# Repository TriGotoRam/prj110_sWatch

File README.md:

My custom sWatch in standart china case. main CPU - ESP32. LCD - 160*80 16bit color + accelerometer + IRRED pulse meter.
Contains:
Eagle pcb
ESP32 sorces

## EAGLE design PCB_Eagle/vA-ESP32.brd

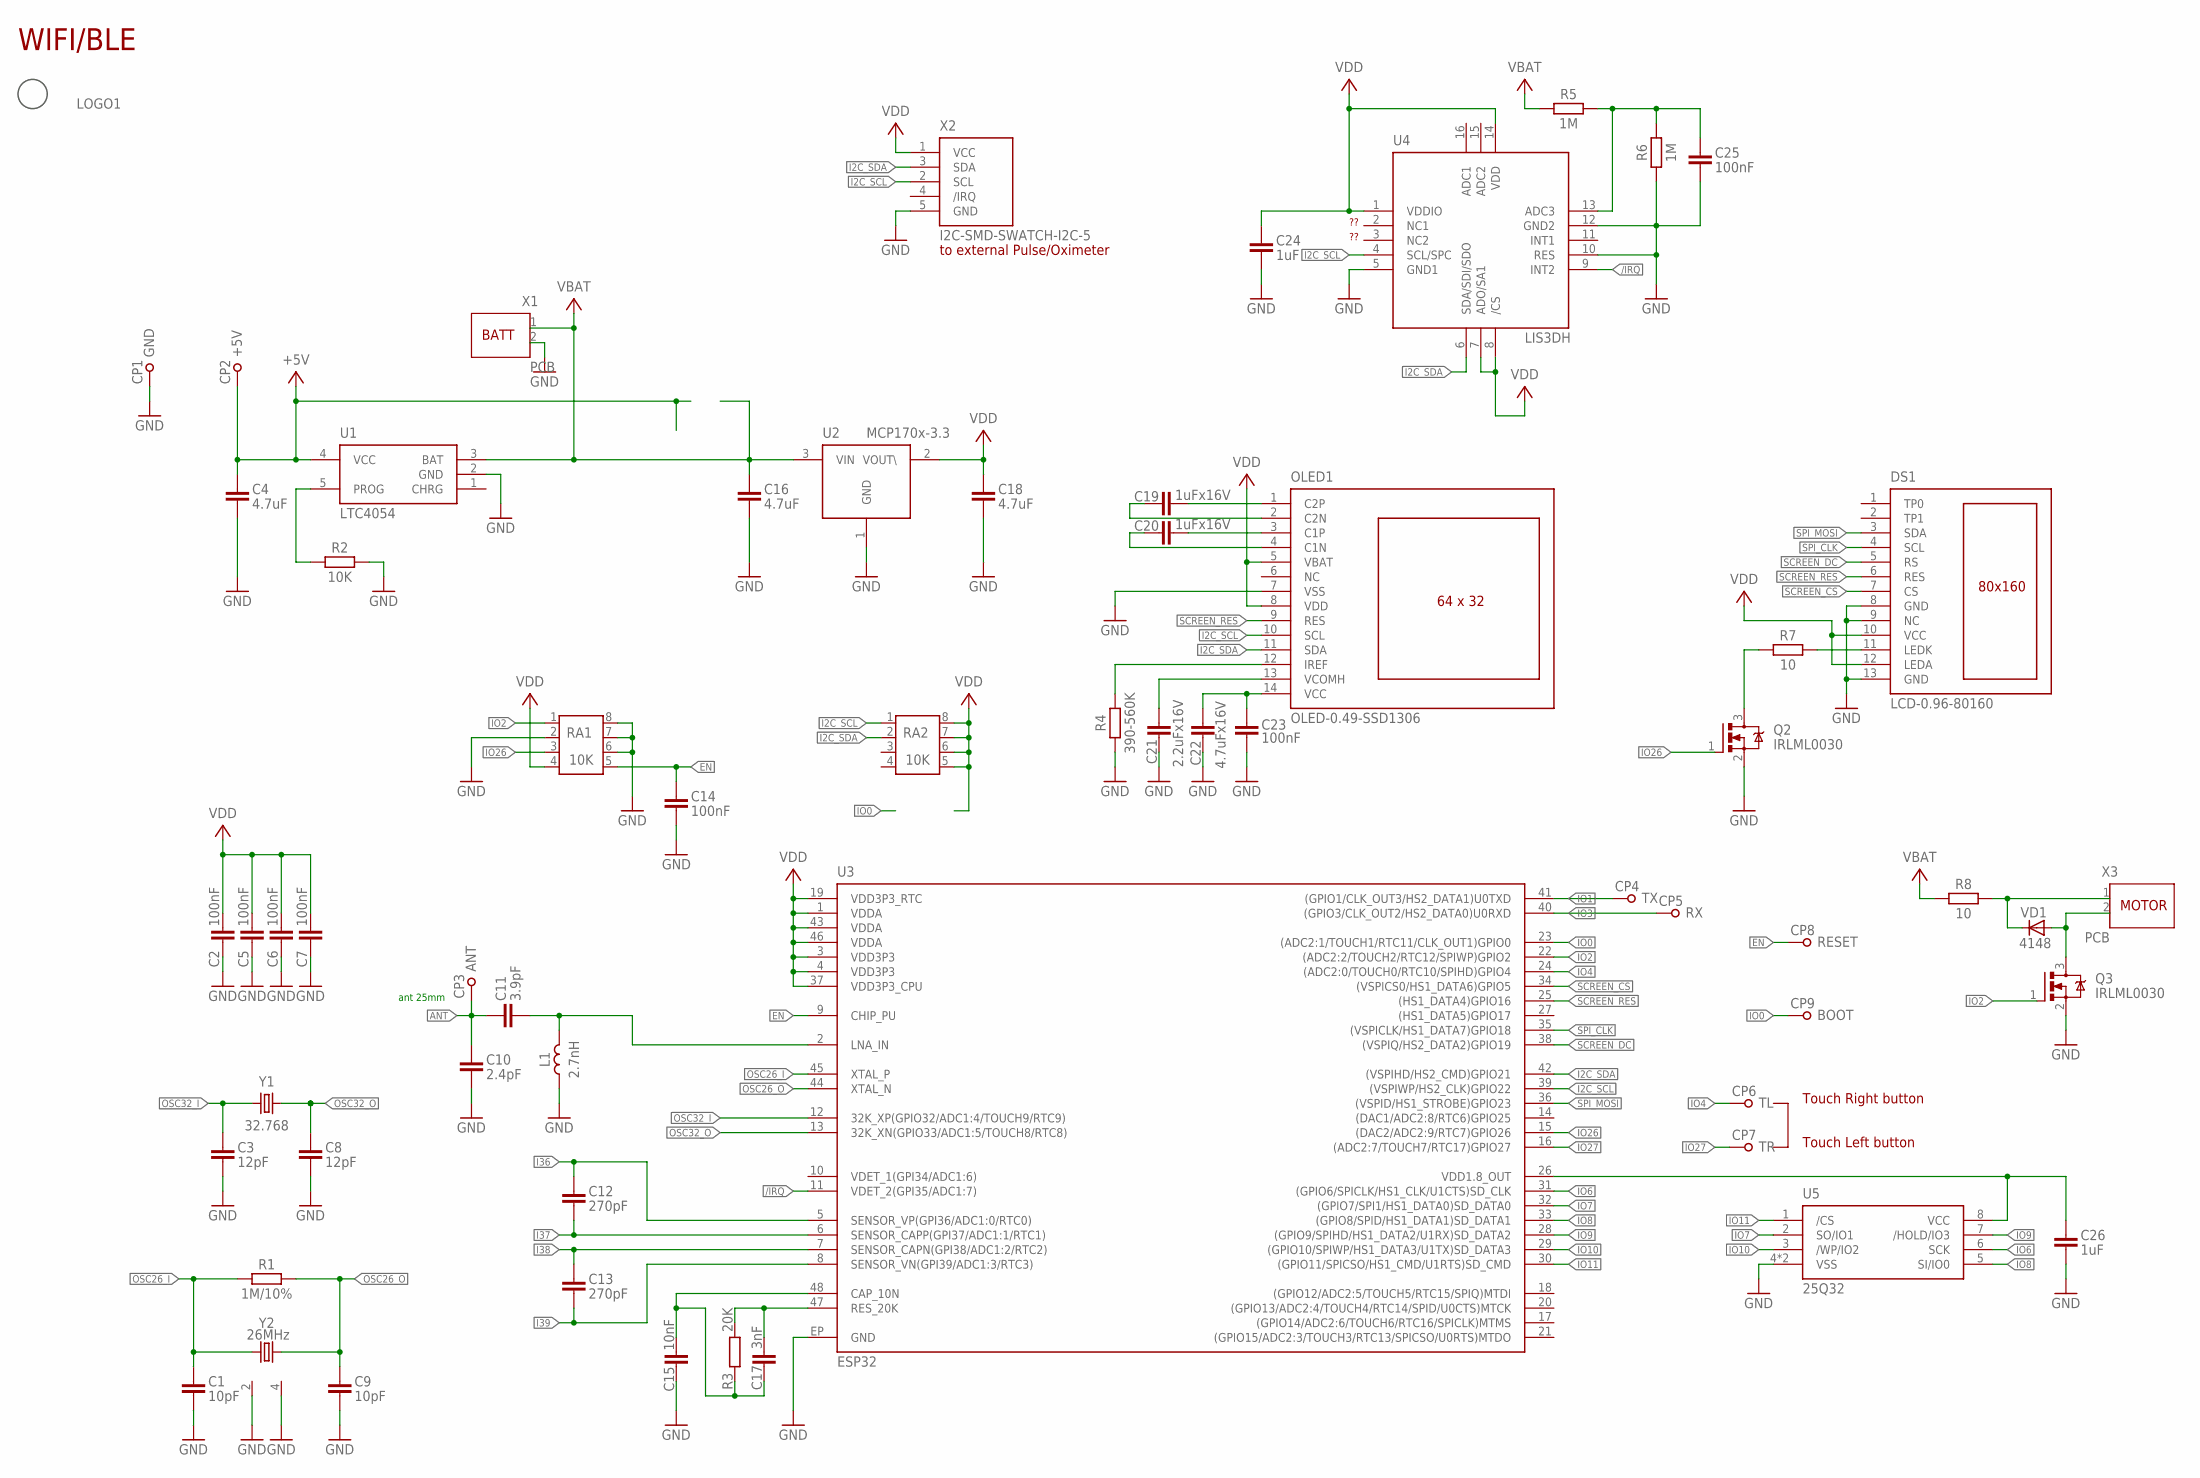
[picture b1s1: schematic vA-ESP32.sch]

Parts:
C1, C9: 10pF; C0402
C2, C6, C7, C14, C25: 100nF; C0402
C3, C8: 12pF; C0402
C4, C16, C18: 4.7uF; C0603
C5, C23: 100nF; C0603
C10: 2.4pF; C0402
C11: 3.9pF; C0402
C12, C13: 270pF; C0402
C15: 10nF; C0402
C17: 3nF; C0402
C19, C20: 1uFx16V; C0603
C21: 2.2uFx16V; C0805
C22: 4.7uFx16V; C0805
C24: 1uF; C0402
C26: 1uF; C0603
CP1: GND; CP-1-R08MM
CP2: +5V; CP-1-R08MM
CP3: ANT; CP-1-C08MM
CP4: TX; CP-1-C08MM
CP5: RX; CP-1-C08MM
CP6: TL; CP-1-C24MM
CP7: TR; CP-1-C24MM
CP8: RESET; CP-1-C08MM
CP9: BOOT; CP-1-C08MM
DS1: LCD-0.96-80160; LCD-0.96-80*160
FIDUCIAL1: FIDUCIAL-MICRO
L1: 2.7nH; L0402
LOGO1: LOGO6; LOGO_OMEGA
OLED1: OLED-0.49-SSD1306; OLED_0.49-SSD1306
Q2, Q3: IRLML0030; SOT23-3-1
R1: 1M/10%; R0402
R2: 10K; R0402
R3: 20K; R0402
R4: 390-560K; R0603
R5, R6: 1M; R0402
R7, R8: 10; R0603
RA1, RA2: 10K; EXB28V
U1: LTC4054; SOT23-5L
U2: MCP170x-3.3; SOT23-3
U3: ESP32; QFN48-6X6-0.4MM
U4: LIS3DH; LGA16
U5: 25Q32; USON-8-2X3
VD1: 4148; SOD523
X1, X3: PCB; 2C_SMD-SWATCH
X2: I2C-SMD-SWATCH-I2C-5; SMD-SWATCH-I2C-5
Y1: 32.768; XTAL3215
Y2: 26MHz; CRYSTAL-SMD-3225

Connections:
+5V: C4.1, CP2.1, U1.4 (VCC)
/IRQ: U3.11 (VDET_2(GPI35/ADC1:7)), U4.9 (INT2)
ANT: C10.1, C11.1, CP3.1
EN: C14.1, CP8.1, RA1.5, U3.9 (CHIP_PU)
GND: C1.2, C2.2, C3.2, C4.2, C5.2, C6.2, C7.2, C8.2, C9.2, C10.2, C14.2, C15.2, C16.2, C18.2, C21.2, C22.2, C23.2, C24.2, C25.2, C26.2, CP1.1, DS1.8 (GND), DS1.9 (NC), DS1.13 (GND), L1.1 (%1), OLED1.7 (VSS), Q2.2 (S), Q3.2 (S), R2.2, R4.1, R6.1, RA1.2, RA1.6, RA1.7, RA1.8, U1.2 (GND), U2.1 (GND), U3.EP (GND), U4.5 (GND1), U4.10 (RES), U4.12 (GND2), U5.4 (VSS), U5.P$1 (VSS), X1.2, X2.5 (GND), Y2.2 (S), Y2.4 (S)
I2C_SCL: OLED1.10 (SCL), RA2.1, U3.39 ((VSPIWP/HS2_CLK)GPIO22), U4.4 (SCL/SPC), X2.2 (SCL)
I2C_SDA: OLED1.11 (SDA), RA2.2, U3.42 ((VSPIHD/HS2_CMD)GPIO21), U4.6 (SDA/SDI/SDO), X2.3 (SDA)
I36: C12.1, U3.5 (SENSOR_VP(GPI36/ADC1:0/RTC0))
I37: C12.2, U3.6 (SENSOR_CAPP(GPI37/ADC1:1/RTC1))
I38: C13.1, U3.7 (SENSOR_CAPN(GPI38/ADC1:2/RTC2))
I39: C13.2, U3.8 (SENSOR_VN(GPI39/ADC1:3/RTC3))
IO0: CP9.1, U3.23 ((ADC2:1/TOUCH1/RTC11/CLK_OUT1)GPIO0)
IO1: CP4.1, U3.41 ((GPIO1/CLK_OUT3/HS2_DATA1)U0TXD)
IO2: Q3.1 (G), RA1.1, U3.22 ((ADC2:2/TOUCH2/RTC12/SPIWP)GPIO2)
IO3: CP5.1, U3.40 ((GPIO3/CLK_OUT2/HS2_DATA0)U0RXD)
IO4: CP6.1, U3.24 ((ADC2:0/TOUCH0/RTC10/SPIHD)GPIO4)
IO6: U3.31 ((GPIO6/SPICLK/HS1_CLK/U1CTS)SD_CLK), U5.6 (SCK)
IO7: U3.32 ((GPIO7/SPI1/HS1_DATA0)SD_DATA0), U5.2 (SO/IO1)
IO8: U3.33 ((GPIO8/SPID/HS1_DATA1)SD_DATA1), U5.5 (SI/IO0)
IO9: U3.28 ((GPIO9/SPIHD/HS1_DATA2/U1RX)SD_DATA2), U5.7 (/HOLD/IO3)
IO10: U3.29 ((GPIO10/SPIWP/HS1_DATA3/U1TX)SD_DATA3), U5.3 (/WP/IO2)
IO11: U3.30 ((GPIO11/SPICSO/HS1_CMD/U1RTS)SD_CMD), U5.1 (/CS)
IO26: Q2.1 (G), RA1.3, U3.15 ((DAC2/ADC2:9/RTC7)GPIO26)
IO27: CP7.1, U3.16 ((ADC2:7/TOUCH7/RTC17)GPIO27)
unnamed: C20.2, OLED1.3 (C1P)
unnamed: C17.1, R3.1, U3.47 (RES_20K)
unnamed: C20.1, OLED1.4 (C1N)
unnamed: C15.1, C17.2, R3.2, U3.48 (CAP_10N)
unnamed: C19.1, OLED1.2 (C2N)
unnamed: R2.1, U1.5 (PROG)
unnamed: C11.2, L1.2 (%2), U3.2 (LNA_IN)
unnamed: Q2.3 (D), R7.1
unnamed: C19.2, OLED1.1 (C2P)
unnamed: C22.1, C23.1, OLED1.14 (VCC)
unnamed: C21.1, OLED1.13 (VCOMH)
unnamed: OLED1.12 (IREF), R4.2
unnamed: DS1.11 (LEDK), R7.2
unnamed: Q3.3 (D), VD1.A, X3.2
unnamed: R8.2, VD1.C, X3.1
OSC26_I: C1.1, R1.1, U3.45 (XTAL_P), Y2.1
OSC26_O: C9.1, R1.2, U3.44 (XTAL_N), Y2.3 (2)
OSC32_I: C3.1, U3.12 (32K_XP(GPIO32/ADC1:4/TOUCH9/RTC9)), Y1.1
OSC32_O: C8.1, U3.13 (32K_XN(GPIO33/ADC1:5/TOUCH8/RTC8)), Y1.2
SCREEN_CS: DS1.7 (CS), U3.34 ((VSPICS0/HS1_DATA6)GPIO5)
SCREEN_DC: DS1.5 (RS), U3.38 ((VSPIQ/HS2_DATA2)GPIO19)
SCREEN_RES: DS1.6 (RES), OLED1.9 (RES), U3.25 ((HS1_DATA4)GPIO16)
SPI_CLK: DS1.4 (SCL), U3.35 ((VSPICLK/HS1_DATA7)GPIO18)
SPI_MOSI: DS1.3 (SDA), U3.36 ((VSPID/HS1_STROBE)GPIO23)
VBAT: C16.1, R5.1, R8.1, U1.3 (BAT), U2.3 (VIN), X1.1
VBAT_ADC: C25.1, R5.2, R6.2, U4.13 (ADC3)
VDD: C2.1, C5.1, C6.1, C7.1, C18.1, C24.1, DS1.10 (VCC), DS1.12 (LEDA), OLED1.5 (VBAT), OLED1.8 (VDD), RA1.4, RA2.5, RA2.6, RA2.7, RA2.8, U2.2 (VOUT\), U3.1 (VDDA), U3.3 (VDD3P3), U3.4 (VDD3P3), U3.19 (VDD3P3_RTC), U3.37 (VDD3P3_CPU), U3.43 (VDDA), U3.46 (VDDA), U4.1 (VDDIO), U4.7 (ADO/SA1), U4.8 (/CS), U4.14 (VDD), X2.1 (VCC)
VDD_SDIO: C26.1, U3.26 (VDD1.8_OUT), U5.8 (VCC)

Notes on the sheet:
WIFI/BLE
ant 25mm
Touch Right button
Touch Left button
MOTOR
to external Pulse/Oximeter
BATT

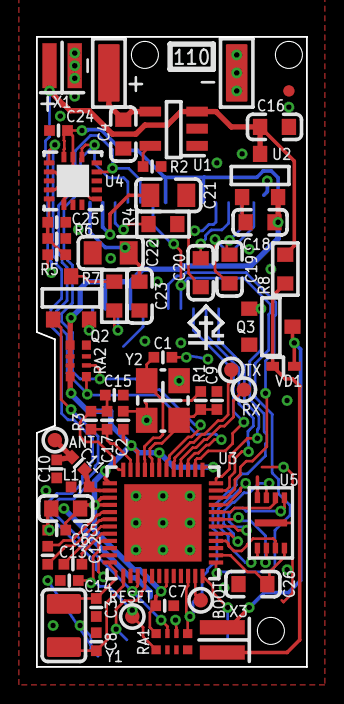
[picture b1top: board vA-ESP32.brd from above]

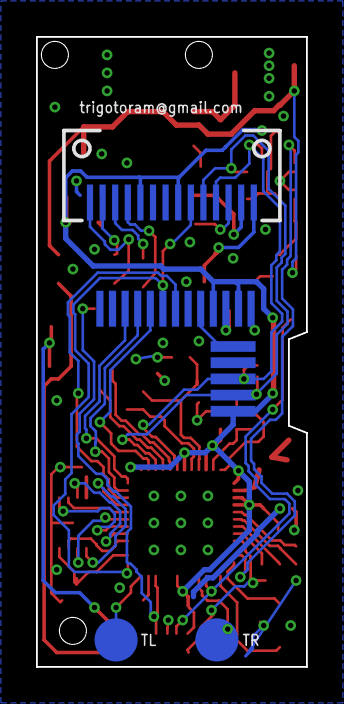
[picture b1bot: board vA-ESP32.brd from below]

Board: 2 copper layers, 15.0 x 35.0 mm, 63 parts (5 on the bottom side), 52 nets.

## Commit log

2018-09-11 add README.md
